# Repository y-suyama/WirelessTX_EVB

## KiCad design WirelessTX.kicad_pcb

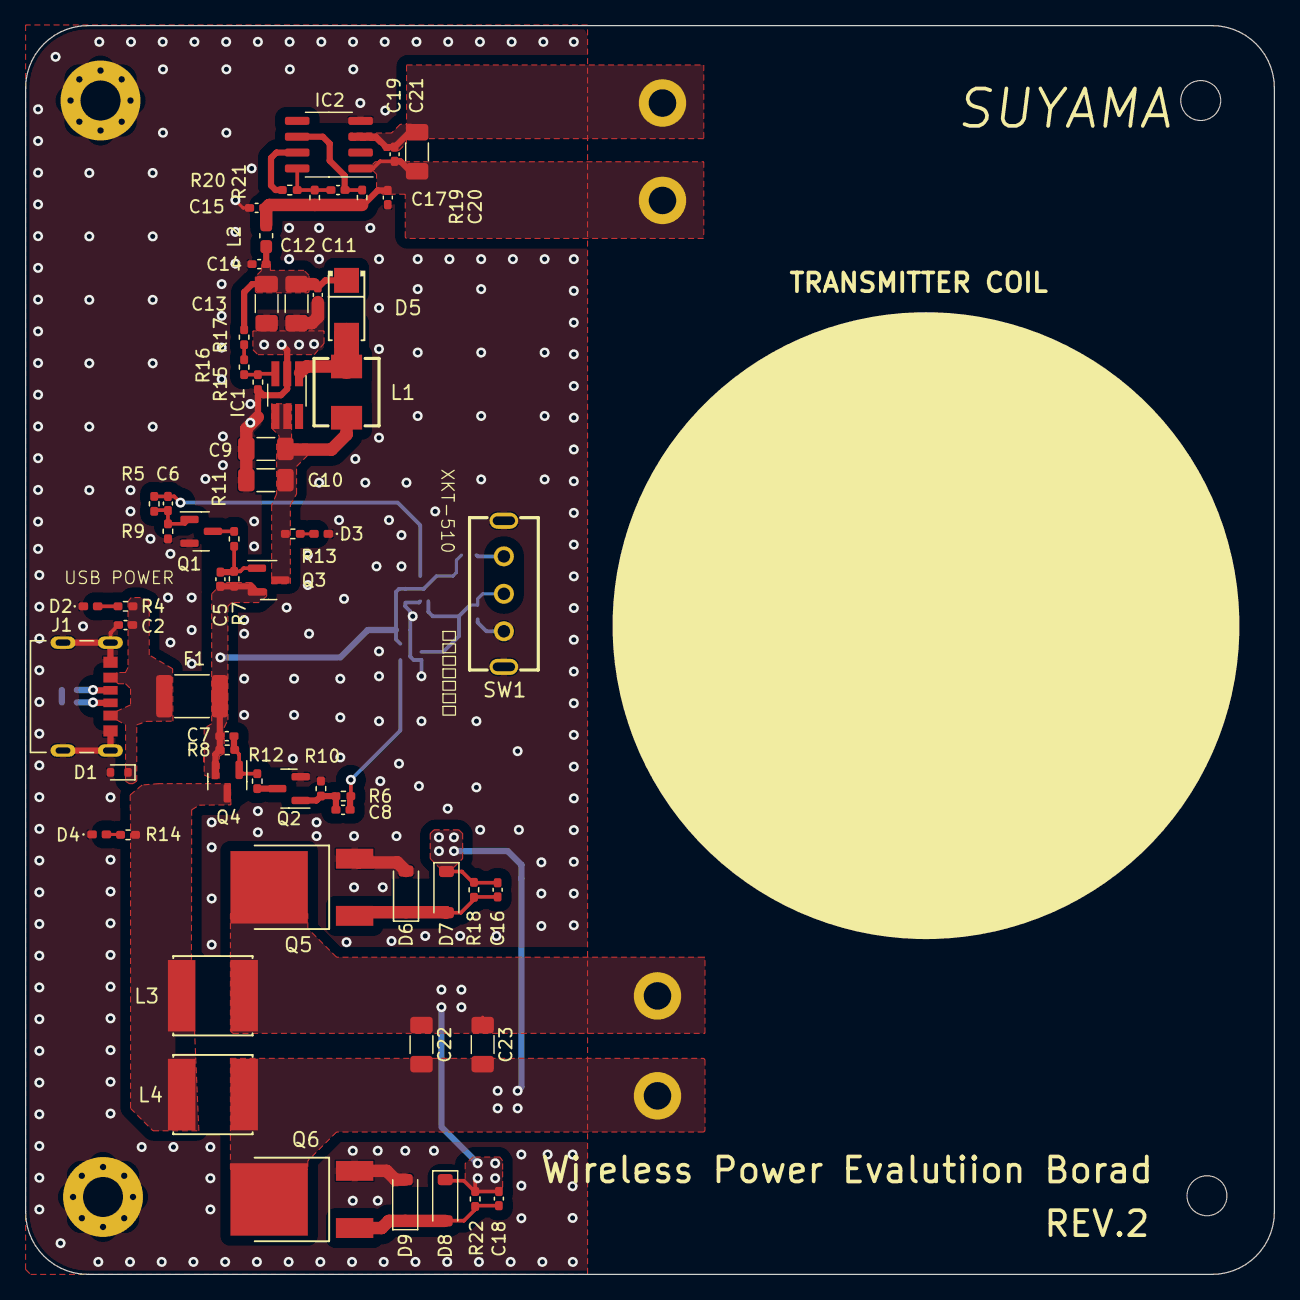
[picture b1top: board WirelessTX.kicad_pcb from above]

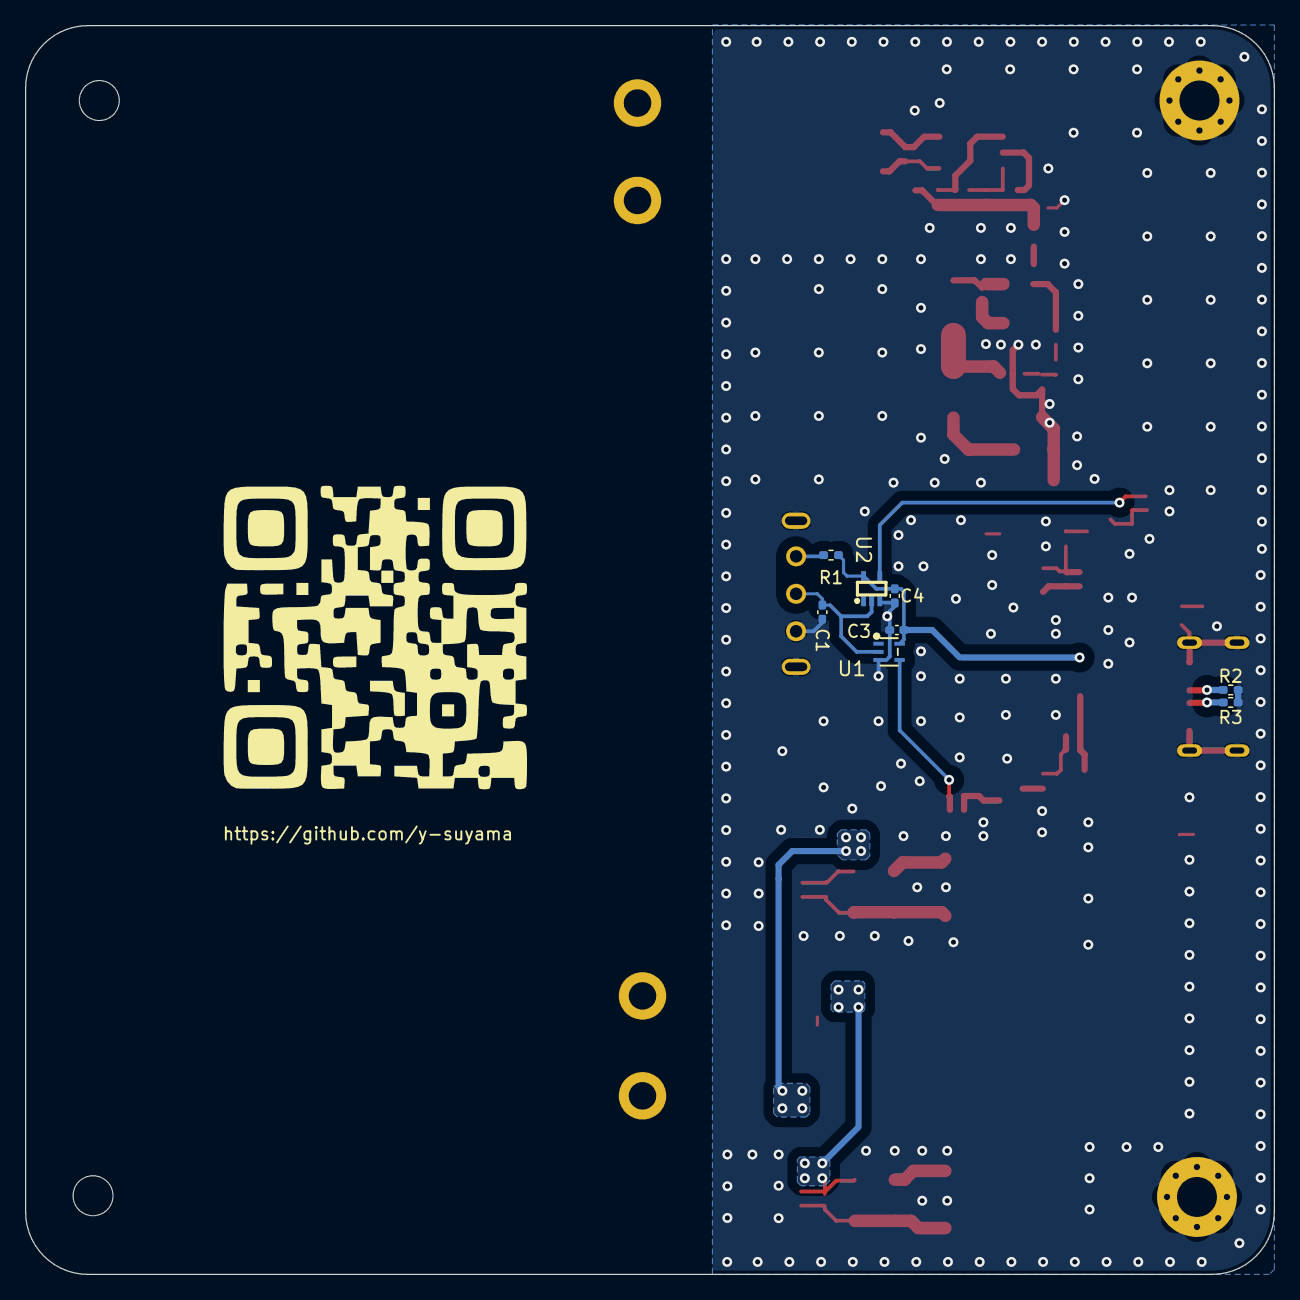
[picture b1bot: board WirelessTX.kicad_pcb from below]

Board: 2 copper layers, 100.0 x 100.0 mm, 71 parts (8 on the bottom side), 33 nets.

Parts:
C1, C2, C3, C4, C5, C7, C11, C14, C15, C20: 0.1u; C_0402_1005Metric_Pad0.74x0.62mm_HandSolder
C6, C8: 47p; C_0402_1005Metric_Pad0.74x0.62mm_HandSolder
C9, C10: 10uF; C_1206_3216Metric_Pad1.33x1.80mm_HandSolder
C12, C13, C21: 22uF; C_1206_3216Metric_Pad1.33x1.80mm_HandSolder
C16, C18: 0.01uF; C_0402_1005Metric_Pad0.74x0.62mm_HandSolder
C17: 120pF; C_0402_1005Metric_Pad0.74x0.62mm_HandSolder
C19: 27nF; C_0402_1005Metric_Pad0.74x0.62mm_HandSolder
C22, C23: 0.15u; C_1206_3216Metric_Pad1.33x1.80mm_HandSolder
D1: LESD5D5-0CT1G; D_SOD-523
D2: XL-1005UBC; LED_0402_1005Metric_Pad0.77x0.64mm_HandSolder
D3: XL-1005UWC; LED_0402_1005Metric_Pad0.77x0.64mm_HandSolder
D4: XL-1005UYC; LED_0402_1005Metric_Pad0.77x0.64mm_HandSolder
D5: SS34
D6, D9: BZT52C16; D_SOD-123
D7, D8: B5819W; D_SOD-123
F1: K1812L30012DR
IC1: SX1308; TSOT-23-6_HandSoldering
IC2: XKT510; SOP-8_3.76x4.96mm_P1.27mm
J1: UJC-HP-3-SMT-TR; CUI_UJC-HP-3-SMT-TR
L1: FXL0530-100-M
L2: FBMH1608HM101; L_0603_1608Metric_Pad1.05x0.95mm_HandSolder
L3, L4: 68uH; IND-SMD_L6.0-W6.0
Q1, Q2: 2SC1815; SOT-23
Q3, Q4: HL3401; SOT-23
Q5, Q6: 30N06; TO-252-2_L6.6-W6.1-P4.57-LS9.9-BR-CW
R1, R5, R6, R9, R10: 10k; R_0402_1005Metric_Pad0.72x0.64mm_HandSolder
R2, R3: 5.1k; R_0402_1005Metric_Pad0.72x0.64mm_HandSolder
R4, R13, R14: 1k; R_0402_1005Metric_Pad0.72x0.64mm_HandSolder
R7, R8: 3k; R_0402_1005Metric_Pad0.72x0.64mm_HandSolder
R11, R12: 330; R_0402_1005Metric_Pad0.72x0.64mm_HandSolder
R15: 8.2k; R_0402_1005Metric_Pad0.72x0.64mm_HandSolder
R16: 100k; R_0402_1005Metric_Pad0.72x0.64mm_HandSolder
R17: 15k; R_0402_1005Metric_Pad0.72x0.64mm_HandSolder
R18, R22: 100; R_0402_1005Metric_Pad0.72x0.64mm_HandSolder
R19, R21: 47k; R_0402_1005Metric_Pad0.72x0.64mm_HandSolder
R20: 9.1k; R_0402_1005Metric_Pad0.72x0.64mm_HandSolder
SW1: SS12F44G4; SW-TH_SHOU-HAN_SS12F44G4
U1: 74AHC1G14SE-7; SOT-353_L2.1-W1.3-P0.65-LS2.3-BR
U2: 74LVCE1G126SE-7; SOT-353_L2.2-W1.4-P0.65-LS2.4-BL

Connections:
+5V: C2.1, D1.1 (A1), F1.2, J1.A9 (V-BUS), J1.B9 (V-BUS__1), R4.1
+5V_DISC: L3.2, L4.1, Q4.3 (D), R14.1
+5V_PSW: C3.1, C4.1, C5.1, C7.1, F1.1, Q3.2 (S), Q4.2 (S), R1.1, R7.1, R8.1, U1.5 (VCC), U2.5 (VCC)
+9V: C15.1, C19.1, C20.1, C21.1, IC2.1 (V+), L2.2, R19.2, R21.1
GND: C1.2, C2.2, C3.2, C4.2, C9.2, C10.2, C11.2, C12.2, C13.2, C14.2, C15.2, C20.2, D1.2 (A2), D2.1 (K), D3.1 (K), D4.1 (K), D6.2 (A), D9.2 (A), IC1.2 (GND), IC2.4 (GND), J1.A12 (GND), J1.B12 (GND__1), J1.S1 (SHIELD), J1.S2 (SHIELD__1), J1.S3 (SHIELD__2), J1.S4 (SHIELD__3), Q1.2 (E), Q2.2 (E), Q5.3 (S), Q6.3 (S), R2.2, R3.2, R9.2, R10.2, R15.2, SW1.3 (C), SW1.4 (D), SW1.5 (E), U1.3 (GND), U2.3 (GND)
unnamed: D2.2 (A), R4.2
unnamed: D3.2 (A), R13.2
unnamed: D4.2 (A), R14.2
unnamed: D5.2 (A), IC1.1 (SW), L1.2
unnamed: C11.1, C12.1, C13.1, C14.1, D5.1 (K), L2.1, R17.1
unnamed: C16.2, D6.1 (K), D7.2 (A), Q5.1 (G), R18.2
unnamed: C16.1, C22.2, C23.2, D7.1 (K), L4.2, Q6.2 (D), R18.1
unnamed: C18.2, D8.2 (A), D9.1 (K), Q6.1 (G), R22.2
unnamed: C18.1, C22.1, C23.1, D8.1 (K), L3.1, Q5.2 (D), R22.1
unnamed: C9.1, C10.1, IC1.4 (EN), IC1.5 (IN), L1.1, Q3.3 (D), R13.1
unnamed: IC1.3 (FB), R15.1, R16.2
unnamed: C17.2, IC2.6 (AIN), R19.1
unnamed: IC2.7 (FIN), R20.2
unnamed: C17.1, IC2.8 (NC), R20.1, R21.2
unnamed: C19.2, C21.2, IC2.3 (OUT)
unnamed: J1.A5 (CC1), R2.1
unnamed: J1.B5 (CC2), R3.1
unnamed: C6.1, Q1.1 (B), R5.2, R9.1
unnamed: Q1.3 (C), R11.2
unnamed: C8.1, Q2.1 (B), R6.2, R10.1
unnamed: Q2.3 (C), R12.2
unnamed: C5.2, Q3.1 (G), R7.2, R11.1
unnamed: C7.2, Q4.1 (G), R8.2, R12.1
unnamed: R16.1, R17.2
unnamed: R1.2, SW1.1 (A)
unnamed: C1.1, SW1.2 (B), U1.2, U2.2
TXSEL: C6.2, R5.1, U2.4
TXSEL_N: C8.2, R6.1, U1.4
